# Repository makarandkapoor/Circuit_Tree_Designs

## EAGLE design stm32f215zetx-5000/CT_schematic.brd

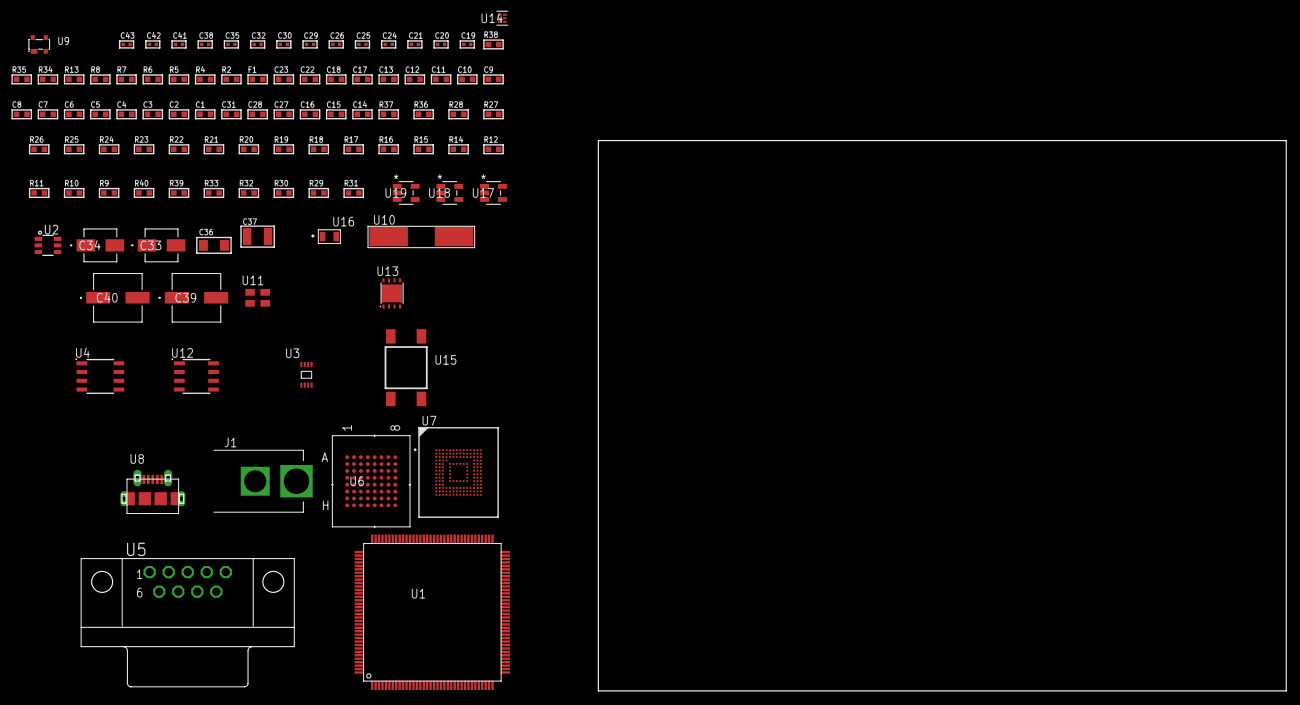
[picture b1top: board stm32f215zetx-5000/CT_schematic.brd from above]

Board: 2 copper layers, 102 parts (0 on the bottom side), 98 nets, no tracks yet.

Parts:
C1, C18, C22, C23: 1e-06; C0603
C2, C3, C4, C5, C6, C7, C8, C9, C10, C11, C12, C13: 1e-07; C0603
C14: 4.7e-06; C0603
C15, C16, C27, C28, C31: 2.2e-06; C0603
C17: 1e-08; C0603
C19, C20: 1e-11; C0402
C21, C24, C25, C32, C35, C41, C42, C43: 1e-08; C0402
C26, C29, C30, C38: 1e-07; C0402
C33: 1e-06; EXV-9B
C34: 2.2e-06; EXV-9B
C36: 1e-05; C1206
C37: 1e-05; C1210
C39, C40: 0.0001; EXV-9H
F1: 240.0; L0603
J1: PJ-037B; PJ-037B_PACKAGE
R2, R35: 1000.0; R0603
R4, R5, R6: 4700.0; R0603
R7, R8: 2200.0; R0603
R9: 47000.0; R0603
R10, R11, R12, R14, R15, R16, R17, R18, R36, R37: 10000.0; R0603
R13: 120.0; R0603
R19, R20, R21, R22, R23, R24, R25, R26, R27, R28: 34000.0; R0603
R29, R30, R32, R33: 100000.0; R0603
R31: 164658.62; R0603
R34: 3900.0; R0603
R38: 9100.0; R0603
R39: 680000.0; R0603
R40: 120000.0; R0603
U1: STM32F215ZET6; LQFP144
U2: MAX4995AAUT+T; SOT-23-6
U3: 24AA01T-I/MNY; TDFN-8/6MM
U4: MCP2562-E/SN; SOIC-8
U5: 182-009-113R531; 182-009-MALE
U6: mt28ew512aba1HPC-0AAT; LBGA-64
U7: mtfc4gmcdm; TFBGA-153
U8: 47590-0001; MICRO_USB_AB
U9: prtr5v0u2ax; SOT143B
U10: ABLS-25.000MHZ-B2F-T
U11: ASEK-32.768KHz-ECST; ASEK
U12: LP2954AIMX/NOPB; LP2954
U13: LP3878SDX-ADJ/NOPB; WSON-8
U14: TPS3895ADRYR; SON-6
U15: 4-1437565-2; SW_4-1437565-2
U16: Q65110A2395; LGM67K-G1J2-24-Z
U17, U18, U19: nc7sz125m5x; NC7SZ125M5X

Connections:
CLK_CRYSTAL_U1_23: C19.1, U1.23, U10.1
CLK_CRYSTAL_U1_24: C20.1, U1.24, U10.2
CLK_U1_8: U1.8, U11.3
GND: C1.2, C2.2, C3.2, C4.2, C5.2, C6.2, C7.2, C8.2, C9.2, C10.2, C11.2, C12.2, C13.2, C14.2, C15.2, C16.2, C17.2, C18.2, C19.2, C20.2, C21.2, C22.2, C23.2, C24.2, C25.2, C26.2, C27.2, C28.2, C29.2, C30.2, C31.2, C32.2, C33.2, C34.2, C35.2, C36.2, C37.2, C38.2, C39.2, C40.2, C41.2, C42.2, C43.2, J1.2, R2.2, R9.2, R10.2, R12.2, R32.2, R35.2, R38.2, R40.2, U1.16, U1.31, U1.38, U1.51, U1.61, U1.83, U1.94, U1.107, U1.120, U1.130, U2.2, U3.4, U4.2, U4.8, U5.5, U6.E8, U6.H2, U6.H7, U7.C4, U7.E7, U7.G5, U7.H10, U7.K8, U7.N2, U7.N5, U7.P4, U7.P6, U8.5, U8.6, U8.7, U8.8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
NET_U1_25: R6.1, U1.25, U19.4
NET_U1_33: C17.1, C18.1, F1.1, U1.32, U1.33
NET_U1_71: C15.1, U1.71
NET_U1_106: C16.1, U1.106
NET_U1_136: R7.1, U1.136, U3.6
NET_U1_137: R8.1, U1.137, U3.5
NET_U1_138: R10.1, U1.138
NET_U1_142: U15.3, U15.4
NET_U2_1: U1.101, U2.1
NET_U2_3: R9.1, U2.3
NET_U4_6: R13.2, U4.6
NET_U5_2: R13.2, U4.6, U5.2
NET_U5_3: R13.1, U4.7, U5.3
NET_U6_B4: R17.1, U6.B4
NET_U6_B5: R4.1, U6.B5, U17.4
NET_U6_F7: R18.1, U6.F7
NET_U7_C2: C28.1, C29.1, U7.C2
NET_U7_K5: R5.1, U7.K5, U18.4
NET_U12_3: R30.1, U12.3
NET_U12_5: R29.1, U12.5
NET_U12_7: R31.2, R32.1, U12.7
NET_U13_1: C35.1, U13.1
NET_U13_6: R34.2, R35.1, U13.6
NET_U13_8: R33.1, U13.8
NET_U14_1: R37.1, R38.1, U14.1
NET_U14_3: R39.2, R40.1, U14.3
NET_U14_4: R36.1, U14.4, U17.2, U18.2, U19.2
NET_U15_1: R2.1, U15.1, U15.2
PROC_CAN1_RX: U1.103, U4.4
PROC_CAN1_TX: U1.104, U4.1
PROC_FSMC_A0: U1.10, U6.E2
PROC_FSMC_A1: U1.11, U6.D2
PROC_FSMC_A2: U1.12, U6.C2
PROC_FSMC_A3: U1.13, U6.A2
PROC_FSMC_A4: U1.14, U6.B2
PROC_FSMC_A5: U1.15, U6.D3
PROC_FSMC_A6: U1.50, U6.C3
PROC_FSMC_A7: U1.53, U6.A3
PROC_FSMC_A8: U1.54, U6.B6
PROC_FSMC_A9: U1.55, U6.A6
PROC_FSMC_A10: U1.56, U6.C6
PROC_FSMC_A11: U1.57, U6.D6
PROC_FSMC_A12: U1.87, U6.B7
PROC_FSMC_A13: U1.88, U6.A7
PROC_FSMC_A14: U1.89, U6.C7
PROC_FSMC_A15: U1.90, U6.D7
PROC_FSMC_A16: U1.80, U6.E7
PROC_FSMC_A17: U1.81, U6.B3
PROC_FSMC_A18: U1.82, U6.C4
PROC_FSMC_A19: U1.2, U6.D5
PROC_FSMC_A20: U1.3, U6.D4
PROC_FSMC_A21: U1.4, U6.C5
PROC_FSMC_A22: U1.5, U6.B8
PROC_FSMC_A23: U1.1, U6.C8
PROC_FSMC_A24: U1.128, U6.F8
PROC_FSMC_D0: U1.85, U6.E3
PROC_FSMC_D1: U1.86, U6.H3
PROC_FSMC_D2: U1.114, U6.E4
PROC_FSMC_D3: U1.115, U6.H4
PROC_FSMC_D4: U1.58, U6.H5
PROC_FSMC_D5: U1.59, U6.E5
PROC_FSMC_D6: U1.60, U6.H6
PROC_FSMC_D7: U1.63, U6.E6
PROC_FSMC_D8: U1.64, U6.F3
PROC_FSMC_D9: U1.65, U6.G3
PROC_FSMC_D10: U1.66, U6.F4
PROC_FSMC_D11: U1.67, U6.G4
PROC_FSMC_D12: U1.68, U6.F5
PROC_FSMC_D13: U1.77, U6.G6
PROC_FSMC_D14: U1.78, U6.F6
PROC_FSMC_D15: U1.79, U6.G7
PROC_FSMC_NE4: R14.1, U1.127, U6.F2
PROC_FSMC_NOE: R15.1, U1.118, U6.G2
PROC_FSMC_NWAIT: U1.122, U6.A4
PROC_FSMC_NWE: R16.1, U1.119, U6.A5
PROC_GPIO_TO_U1_USB_FAULT: R11.1, U1.9, U2.6
PROC_GPIO_TO_U1_VBUS_EN: R12.1, U1.7, U2.4
PROC_SDIO_CK: R28.1, U1.113, U7.M6
PROC_SDIO_CMD: R27.1, U1.116, U7.M5
PROC_SDIO_D0: R19.1, U1.98, U7.A3
PROC_SDIO_D1: R20.1, U1.99, U7.A4
PROC_SDIO_D2: R21.1, U1.111, U7.A5
PROC_SDIO_D3: R22.1, U1.112, U7.B2
PROC_SDIO_D4: R23.1, U1.139, U7.B3
PROC_SDIO_D5: R24.1, U1.140, U7.B4
PROC_SDIO_D6: R25.1, U1.96, U7.B5
PROC_SDIO_D7: R26.1, U1.97, U7.B6
PROC_USB_OTG_HS_DM: U1.75, U8.2, U9.3
PROC_USB_OTG_HS_DP: U1.76, U8.3, U9.2
PROC_USB_OTG_HS_ID: U1.73, U8.4
PROC_USB_OTG_HS_VBUS: U1.74, U8.1, U9.4
VCC_S1_10V6: C33.1, C36.1, C39.1, C40.1, J1.1, R30.2, R33.2, U12.8, U13.4
VCC_TIER1_3V3: C1.1, C2.1, C3.1, C4.1, C5.1, C6.1, C7.1, C8.1, C9.1, C10.1, C11.1, C12.1, C13.1, C14.1, C21.1, C23.1, C24.1, C25.1, C26.1, C27.1, C30.1, C31.1, C32.1, C34.1, C38.1, C41.1, C42.1, C43.1, F1.2, R4.2, R5.2, R6.2, R7.2, R8.2, R11.2, R14.2, R15.2, R16.2, R17.2, R18.2, R19.2, R20.2, R21.2, R22.2, R23.2, R24.2, R25.2, R26.2, R27.2, R28.2, R29.2, R31.1, R36.2, R37.2, R39.1, U1.6, U1.17, U1.30, U1.39, U1.52, U1.62, U1.72, U1.84, U1.95, U1.108, U1.121, U1.131, U1.144, U3.7, U3.8, U4.5, U6.D8, U6.F1, U6.G5, U7.C6, U7.E6, U7.F5, U7.J10, U7.K9, U7.M4, U7.N4, U7.P3, U7.P5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
VCC_TIER1_5V0: C22.1, C37.1, R34.1, U2.5, U4.3, U13.5

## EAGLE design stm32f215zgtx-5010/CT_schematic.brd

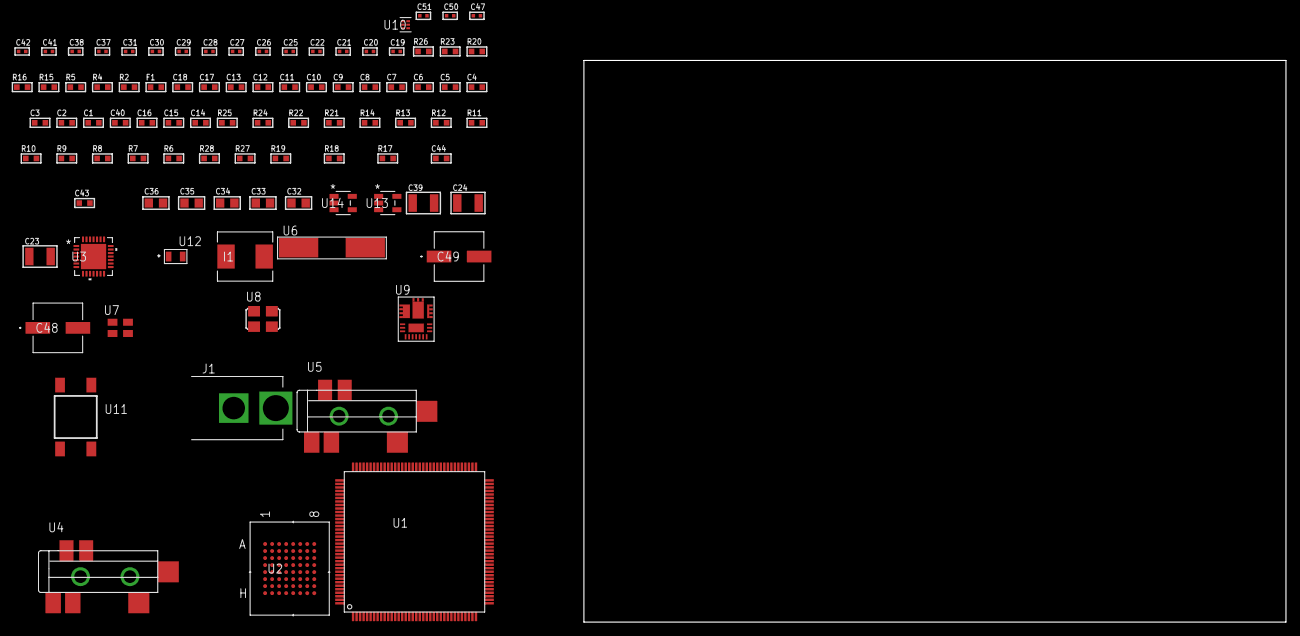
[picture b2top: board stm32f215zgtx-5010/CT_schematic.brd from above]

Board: 2 copper layers, 100.0 x 80.0 mm, 92 parts (0 on the bottom side), 82 nets, no tracks yet.

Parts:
C1, C18: 1e-06; C0603
C2, C3, C4, C5, C6, C7, C8, C9, C10, C11, C12, C13: 1e-07; C0603
C14: 4.7e-06; C0603
C15, C16, C40: 2.2e-06; C0603
C17: 1e-08; C0603
C19, C20: 1e-11; C0402
C21, C22, C37, C38, C50, C51: 1e-08; C0402
C23, C24: 2.2e-05; C1210
C25, C26: 1e-09; C0402
C27, C28, C29, C30, C31, C41, C42, C47: 1e-07; C0402
C32, C33, C34, C35, C36: 1e-05; C0805
C39: 0.0001; C1210
C43: 8.8006443804346e-09; R0603
C44: 3.0002196751482e-07; R0603
C48, C49: 0.0001; EXV-9H
F1: 240.0; L0603
I1: 6.8e-07; IND25X25CZ
J1: PJ-037B; PJ-037B_PACKAGE
R2: 1000.0; R0603
R4, R5: 4700.0; R0603
R6, R7, R8, R9, R10, R11, R24, R25: 10000.0; R0603
R12, R13, R14: 47000.0; R0603
R15: 680.0; R0603
R16: 0.1; R0603
R17: 4030.2416170974; R0603
R18: 719.68600305311; R0603
R19: 57.923764705882; R0603
R20: 130.0; R0603
R21: 39000.0; R0603
R22: 49900.0; R0603
R23: 5100.0; R0603
R26: 9100.0; R0603
R27: 680000.0; R0603
R28: 120000.0; R0603
U1: STM32F215ZGT7; LQFP144
U2: mt28ew512aba1HPC-0AAT; LBGA-64
U3: WM8731CLSEFL; QFN-28
U4, U5: SJ-43515TS-SMT-TR
U6: ABLS-25.000MHZ-B2F-T
U7: ASEK-32.768KHz-ECST; ASEK
U8: ASFL1-12.288MHZ-EC-T; ASFL1
U9: IR3899MTR1PBF
U10: TPS3895ADRYR; SON-6
U11: 4-1437565-2; SW_4-1437565-2
U12: Q65110A2395; LGM67K-G1J2-24-Z
U13, U14: nc7sz125m5x; NC7SZ125M5X

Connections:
CLK_CRYSTAL_U1_23: C19.1, U1.23, U6.1
CLK_CRYSTAL_U1_24: C20.1, U1.24, U6.2
CLK_U1_8: U1.8, U7.3
CLK_U3_1: U3.1, U8.3
GND: C1.2, C2.2, C3.2, C4.2, C5.2, C6.2, C7.2, C8.2, C9.2, C10.2, C11.2, C12.2, C13.2, C14.2, C15.2, C16.2, C17.2, C18.2, C19.2, C20.2, C21.2, C22.2, C26.2, C27.2, C28.2, C29.2, C30.2, C31.2, C32.2, C33.2, C34.2, C35.2, C36.2, C37.2, C38.2, C40.2, C41.2, C42.2, C47.2, C48.2, C49.2, C50.2, C51.2, J1.2, R2.2, R6.2, R12.2, R13.2, R14.2, R16.1, R16.2, R18.2, R21.2, R23.2, R26.2, R28.2, U1.16, U1.31, U1.38, U1.51, U1.61, U1.83, U1.94, U1.107, U1.120, U1.130, U2.E8, U2.H2, U2.H7, U3.4, U3.15, U3.19, U3.25, U3.26, U3.29, U4.1, U5.1, U7.2, U8.2, U9.4, U9.11, U9.17, U10.2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
NET_U1_25: R5.1, U1.25, U14.4
NET_U1_33: C17.1, C18.1, F1.1, U1.32, U1.33
NET_U1_71: C15.1, U1.71
NET_U1_106: C16.1, U1.106
NET_U1_138: R6.1, U1.138
NET_U1_142: U11.3, U11.4
NET_U2_B4: R10.1, U2.B4
NET_U2_B5: R4.1, U2.B5, U13.4
NET_U2_F7: R11.1, U2.F7
NET_U3_20: C31.1, C36.1, U3.20
NET_U4_2: C24.1, R13.1, U4.2
NET_U4_5: C23.1, R12.1, U4.5
NET_U5_5: C25.1, C26.1, R14.1, R15.1, U5.5
NET_U9_1: C43.1, R17.1, R18.1, R19.1, R20.1, U9.1, U9.8
NET_U9_2: C42.1, U9.2
NET_U9_3: C43.2, C44.1, C44.2, U9.3
NET_U9_5: R21.1, U9.5
NET_U9_10: C40.1, U9.10
NET_U9_12: C39.1, I1.1, U9.12
NET_U9_14: C39.2, U9.14
NET_U9_15: R22.1, R23.1, U9.15
NET_U9_ATNET_3: I1.2, R17.2
NET_U9_ATNET_4: C44.2, R19.2
NET_U10_1: R25.1, R26.1, U10.1
NET_U10_3: R27.2, R28.1, U10.3
NET_U10_4: R24.1, U10.4, U13.2, U14.2
NET_U11_1: R2.1, U11.1, U11.2
PROC_FSMC_A0: U1.10, U2.E2
PROC_FSMC_A1: U1.11, U2.D2
PROC_FSMC_A2: U1.12, U2.C2
PROC_FSMC_A3: U1.13, U2.A2
PROC_FSMC_A4: U1.14, U2.B2
PROC_FSMC_A5: U1.15, U2.D3
PROC_FSMC_A6: U1.50, U2.C3
PROC_FSMC_A7: U1.53, U2.A3
PROC_FSMC_A8: U1.54, U2.B6
PROC_FSMC_A9: U1.55, U2.A6
PROC_FSMC_A10: U1.56, U2.C6
PROC_FSMC_A11: U1.57, U2.D6
PROC_FSMC_A12: U1.87, U2.B7
PROC_FSMC_A13: U1.88, U2.A7
PROC_FSMC_A14: U1.89, U2.C7
PROC_FSMC_A15: U1.90, U2.D7
PROC_FSMC_A16: U1.80, U2.E7
PROC_FSMC_A17: U1.81, U2.B3
PROC_FSMC_A18: U1.82, U2.C4
PROC_FSMC_A19: U1.2, U2.D5
PROC_FSMC_A20: U1.3, U2.D4
PROC_FSMC_A21: U1.4, U2.C5
PROC_FSMC_A22: U1.5, U2.B8
PROC_FSMC_A23: U1.1, U2.C8
PROC_FSMC_A24: U1.128, U2.F8
PROC_FSMC_D0: U1.85, U2.E3
PROC_FSMC_D1: U1.86, U2.H3
PROC_FSMC_D2: U1.114, U2.E4
PROC_FSMC_D3: U1.115, U2.H4
PROC_FSMC_D4: U1.58, U2.H5
PROC_FSMC_D5: U1.59, U2.E5
PROC_FSMC_D6: U1.60, U2.H6
PROC_FSMC_D7: U1.63, U2.E6
PROC_FSMC_D8: U1.64, U2.F3
PROC_FSMC_D9: U1.65, U2.G3
PROC_FSMC_D10: U1.66, U2.F4
PROC_FSMC_D11: U1.67, U2.G4
PROC_FSMC_D12: U1.68, U2.F5
PROC_FSMC_D13: U1.77, U2.G6
PROC_FSMC_D14: U1.78, U2.F6
PROC_FSMC_D15: U1.79, U2.G7
PROC_FSMC_NE4: R7.1, U1.127, U2.F2
PROC_FSMC_NOE: R8.1, U1.118, U2.G2
PROC_FSMC_NWAIT: U1.122, U2.A4
PROC_FSMC_NWE: R9.1, U1.119, U2.A5
PROC_I2S2_SCK: U1.69, U3.7
PROC_I2S2_SD: U1.29, U3.8
PROC_I2S2_WS: U1.73, U3.9, U3.11
VCC_S1_17V0: C41.1, C48.1, C49.1, J1.1, R22.2, U9.9
VCC_TIER1_3V3: C1.1, C2.1, C3.1, C4.1, C5.1, C6.1, C7.1, C8.1, C9.1, C10.1, C11.1, C12.1, C13.1, C14.1, C21.1, C22.1, C27.1, C28.1, C29.1, C30.1, C32.1, C33.1, C34.1, C35.1, C37.1, C38.1, C47.1, C50.1, C51.1, F1.2, I1.2, R4.2, R5.2, R7.2, R8.2, R9.2, R10.2, R11.2, R17.2, R24.2, R25.2, R27.1, U1.6, U1.17, U1.30, U1.39, U1.52, U1.62, U1.72, U1.84, U1.95, U1.108, U1.121, U1.131, U1.144, U2.D8, U2.F1, U2.G5, U3.3, U3.5, U3.12, U3.18, U7.4, U8.4, U10.6, U13.5, U14.5

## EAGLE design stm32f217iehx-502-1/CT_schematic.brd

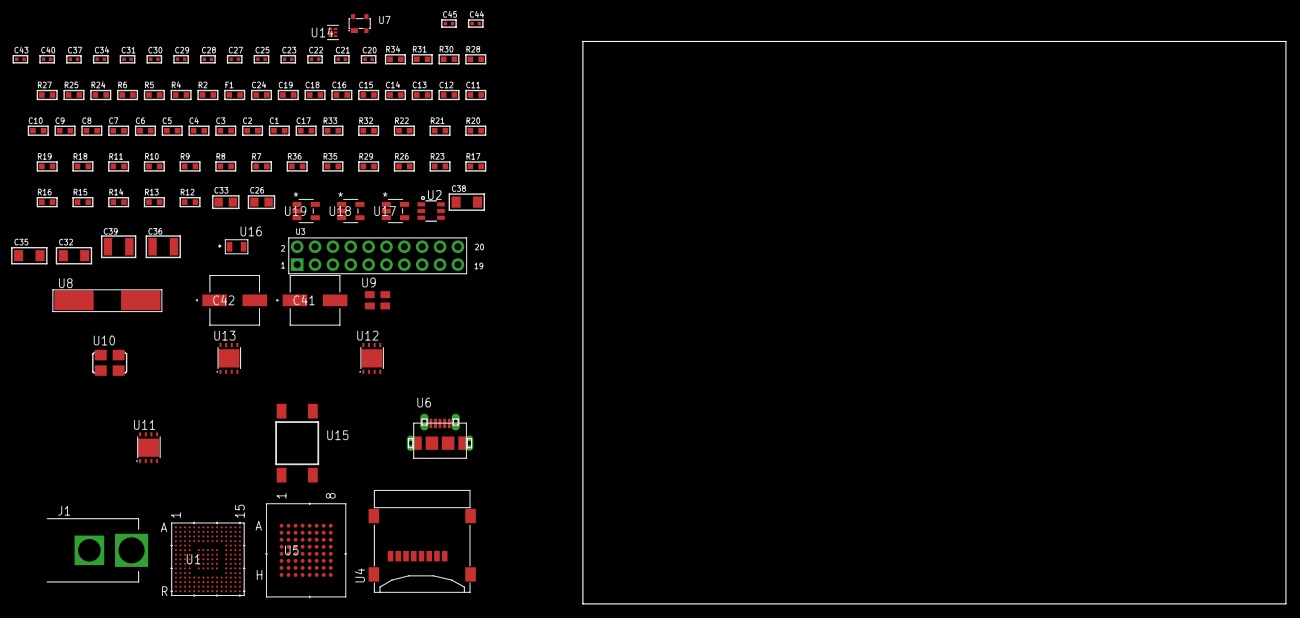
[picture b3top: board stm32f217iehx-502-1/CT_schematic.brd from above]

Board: 2 copper layers, 124.8 x 80.0 mm, 100 parts (0 on the bottom side), 100 nets, no tracks yet.

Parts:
C1, C19, C24: 1e-06; C0603
C2, C3, C4, C5, C6, C7, C8, C9, C10, C11, C12, C13, C14, C15, C16: 1e-07; C0603
C17: 4.7e-06; C0603
C18: 1e-08; C0603
C20, C21, C25, C40: 1e-07; C0402
C22, C23: 1e-11; C0402
C26, C33: 1e-05; C0805
C27, C28, C29, C30, C31, C34, C37, C43, C44, C45: 1e-08; C0402
C32, C35, C38: 1e-05; C1206
C36, C39: 1e-05; C1210
C41, C42: 0.0001; EXV-9H
F1: 240.0; L0603
J1: PJ-037B; PJ-037B_PACKAGE
R2, R25, R28, R31: 1000.0; R0603
R4, R5, R6: 4700.0; R0603
R7: 47000.0; R0603
R8, R9, R10, R11, R18, R19, R20, R21, R22, R32, R33: 10000.0; R0603
R12, R13, R14, R15, R16, R17, R23, R26, R29: 100000.0; R0603
R24: 200.0; R0603
R27: 2231.0; R0603
R30: 3900.0; R0603
R34: 9100.0; R0603
R35: 680000.0; R0603
R36: 120000.0; R0603
U1: STM32F217IEH6; UFBGA176_25
U2: MAX4995AAUT+T; SOT-23-6
U3: arducam_ov2640; ARDUCAM
U4: 0472192001; MOLEX_47219-2001
U5: MT28EW128ABA1HPC-0SIT; LBGA-64
U6: 47590-0001; MICRO_USB_AB
U7: prtr5v0u2ax; SOT143B
U8: ABLS-25.000MHZ-B2F-T
U9: ASEK-32.768KHz-ECST; ASEK
U10: ASFL1-25MHZ-NCS; ASFL1
U11, U12, U13: LP3878SDX-ADJ/NOPB; WSON-8
U14: TPS3895ADRYR; SON-6
U15: 4-1437565-2; SW_4-1437565-2
U16: Q65110A2395; LGM67K-G1J2-24-Z
U17, U18, U19: nc7sz125m5x; NC7SZ125M5X

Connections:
CLK_CRYSTAL_U1_G1: C22.1, U1.G1, U8.1
CLK_CRYSTAL_U1_H1: C23.1, U1.H1, U8.2
CLK_U1_E1: U1.E1, U9.3
CLK_U3_8: U3.8, U10.3
GND: C1.2, C2.2, C3.2, C4.2, C5.2, C6.2, C7.2, C8.2, C9.2, C10.2, C11.2, C12.2, C13.2, C14.2, C15.2, C16.2, C17.2, C18.2, C19.2, C20.2, C21.2, C22.2, C23.2, C24.2, C25.2, C26.2, C27.2, C28.2, C29.2, C30.2, C31.2, C32.2, C33.2, C34.2, C35.2, C36.2, C37.2, C38.2, C39.2, C40.2, C41.2, C42.2, C43.2, C44.2, C45.2, J1.2, R2.2, R7.2, R8.2, R11.2, R25.2, R28.2, R31.2, R34.2, R36.2, U1.D5, U1.D7, U1.D8, U1.D9, U1.F2, U1.F6, U1.F7, U1.F8, U1.F9, U1.F10, U1.F12, U1.G2, U1.G6, U1.G7, U1.G8, U1.G9, U1.G10, U1.G12, U1.H6, U1.H7, U1.H8, U1.H9, U1.H10, U1.H12, U1.J6, U1.J7, U1.J8, U1.J9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
NET_U1_D6: R8.1, U1.D6
NET_U1_F13: C21.1, U1.F13
NET_U1_J1: R5.1, U1.J1, U18.4
NET_U1_L4: R9.1, U1.L4
NET_U1_R1: C18.1, C19.1, F1.1, U1.P1, U1.R1
NET_U1_R15: U15.3, U15.4
NET_U2_3: R7.1, U2.3
NET_U3_19: R6.1, U3.19, U19.4
NET_U5_B4: R21.1, U5.B4
NET_U5_B5: R4.1, U5.B5, U17.4
NET_U11_1: C31.1, U11.1
NET_U11_6: R24.2, R25.1, U11.6
NET_U11_8: R23.1, U11.8
NET_U12_1: C34.1, U12.1
NET_U12_6: R27.2, R28.1, U12.6
NET_U12_8: R26.1, U12.8
NET_U13_1: C37.1, U13.1
NET_U13_6: R30.2, R31.1, U13.6
NET_U13_8: R29.1, U13.8
NET_U14_1: R33.1, R34.1, U14.1
NET_U14_3: R35.2, R36.1, U14.3
NET_U14_4: R32.1, U14.4, U17.2, U18.2, U19.2
NET_U15_1: R2.1, U15.1, U15.2
PROC_DCMI_D0: U1.H15, U3.18
PROC_DCMI_D1: U1.G15, U3.17
PROC_DCMI_D2: U1.L12, U3.16
PROC_DCMI_D3: U1.A3, U3.15
PROC_DCMI_D4: U1.E13, U3.14
PROC_DCMI_D5: U1.B6, U3.13
PROC_DCMI_D6: U1.A5, U3.12
PROC_DCMI_D7: U1.B4, U3.11
PROC_DCMI_D8: U1.D14, U3.10
PROC_DCMI_D9: U1.C14, U3.9
PROC_DCMI_HSYNC: U1.M12, U3.6
PROC_DCMI_PIXCK: U1.P3, U3.7
PROC_DCMI_VSYNC: U1.B5, U3.5
PROC_FSMC_A0: U1.E2, U5.E2
PROC_FSMC_A1: U1.H3, U5.D2
PROC_FSMC_A2: U1.H2, U5.C2
PROC_FSMC_A3: U1.J2, U5.A2
PROC_FSMC_A4: U1.J3, U5.B2
PROC_FSMC_A5: U1.K3, U5.D3
PROC_FSMC_A6: U1.P6, U5.C3
PROC_FSMC_A7: U1.N6, U5.A3
PROC_FSMC_A8: U1.R7, U5.B6
PROC_FSMC_A9: U1.P7, U5.A6
PROC_FSMC_A10: U1.N7, U5.C6
PROC_FSMC_A11: U1.M7, U5.D6
PROC_FSMC_A12: U1.L15, U5.B7
PROC_FSMC_A13: U1.K15, U5.A7
PROC_FSMC_A14: U1.K14, U5.C7
PROC_FSMC_A15: U1.K13, U5.D7
PROC_FSMC_A16: U1.N14, U5.E7
PROC_FSMC_A17: U1.N13, U5.B3
PROC_FSMC_A18: U1.M15, U5.C4
PROC_FSMC_A19: U1.A1, U5.D5
PROC_FSMC_A20: U1.B1, U5.D4
PROC_FSMC_A21: U1.B2, U5.C5
PROC_FSMC_A22: U1.B3, U5.B8
PROC_FSMC_D0: U1.M14, U5.E3
PROC_FSMC_D1: U1.L14, U5.H3
PROC_FSMC_D2: U1.B12, U5.E4
PROC_FSMC_D3: U1.C12, U5.H4
PROC_FSMC_D4: U1.R8, U5.H5
PROC_FSMC_D5: U1.P8, U5.E5
PROC_FSMC_D6: U1.P9, U5.H6
PROC_FSMC_D7: U1.R9, U5.E6
PROC_FSMC_D8: U1.P10, U5.F3
PROC_FSMC_D9: U1.R10, U5.G3
PROC_FSMC_D10: U1.N11, U5.F4
PROC_FSMC_D11: U1.P11, U5.G4
PROC_FSMC_D12: U1.R11, U5.F5
PROC_FSMC_D13: U1.P15, U5.G6
PROC_FSMC_D14: U1.P14, U5.F6
PROC_FSMC_D15: U1.N15, U5.G7
PROC_FSMC_NBL0: R22.1, U1.A4, U5.F7
PROC_FSMC_NE4: R18.1, U1.B8, U5.F2
PROC_FSMC_NOE: R19.1, U1.D10, U5.G2
PROC_FSMC_NWAIT: U1.B11, U5.A4
PROC_FSMC_NWE: R20.1, U1.C11, U5.A5
PROC_GPIO_TO_U1_USB_FAULT: R10.1, U1.A6, U2.6
PROC_GPIO_TO_U1_VBUS_EN: R11.1, U1.A2, U2.4
PROC_SDIO_CK: R13.1, U1.A12, U4.5
PROC_SDIO_CMD: R12.1, U1.D12, U4.3
PROC_SDIO_D0: R14.1, U1.G14, U4.7
PROC_SDIO_D1: R15.1, U1.F14, U4.8
PROC_SDIO_D2: R16.1, U1.B14, U4.1
PROC_SDIO_D3: R17.1, U1.B13, U4.2
PROC_USB_OTG_FS_DM: U6.2, U7.3
PROC_USB_OTG_FS_DP: U6.3, U7.2
PROC_USB_OTG_FS_VBUS: U2.1, U6.1, U7.4
VCC_S1_9V5: C32.1, C35.1, C38.1, C41.1, C42.1, J1.1, R23.2, R26.2, R29.2, U11.4, U12.4, U13.4
VCC_TIER1_1V2: C20.1, C33.1, R24.1, U1.M10, U11.5
VCC_TIER1_3V3: C1.1, C2.1, C3.1, C4.1, C5.1, C6.1, C7.1, C8.1, C9.1, C10.1, C11.1, C12.1, C13.1, C14.1, C15.1, C16.1, C17.1, C24.1, C25.1, C26.1, C27.1, C28.1, C29.1, C30.1, C36.1, C40.1, C43.1, C44.1, C45.1, F1.2, R4.2, R5.2, R6.2, R9.2, R10.2, R12.2, R13.2, R14.2, R15.2, R16.2, R17.2, R18.2, R19.2, R20.2, R21.2, R22.2, R27.1, R32.2, R33.2, R35.1, U1.C1, U1.C5, U1.C7, U1.C8, U1.C9, U1.F3, U1.G3, U1.G13, U1.H13, U1.J12, U1.J13, U1.K4, U1.N8, U1.N9, U1.N10, U3.1, U4.4, U5.D8, U5.F1, U5.G5, U9.4, U10.4, U12.5, U14.6, U17.5, U18.5, U19.5
VCC_TIER1_5V0: C39.1, R30.1, U2.5, U13.5

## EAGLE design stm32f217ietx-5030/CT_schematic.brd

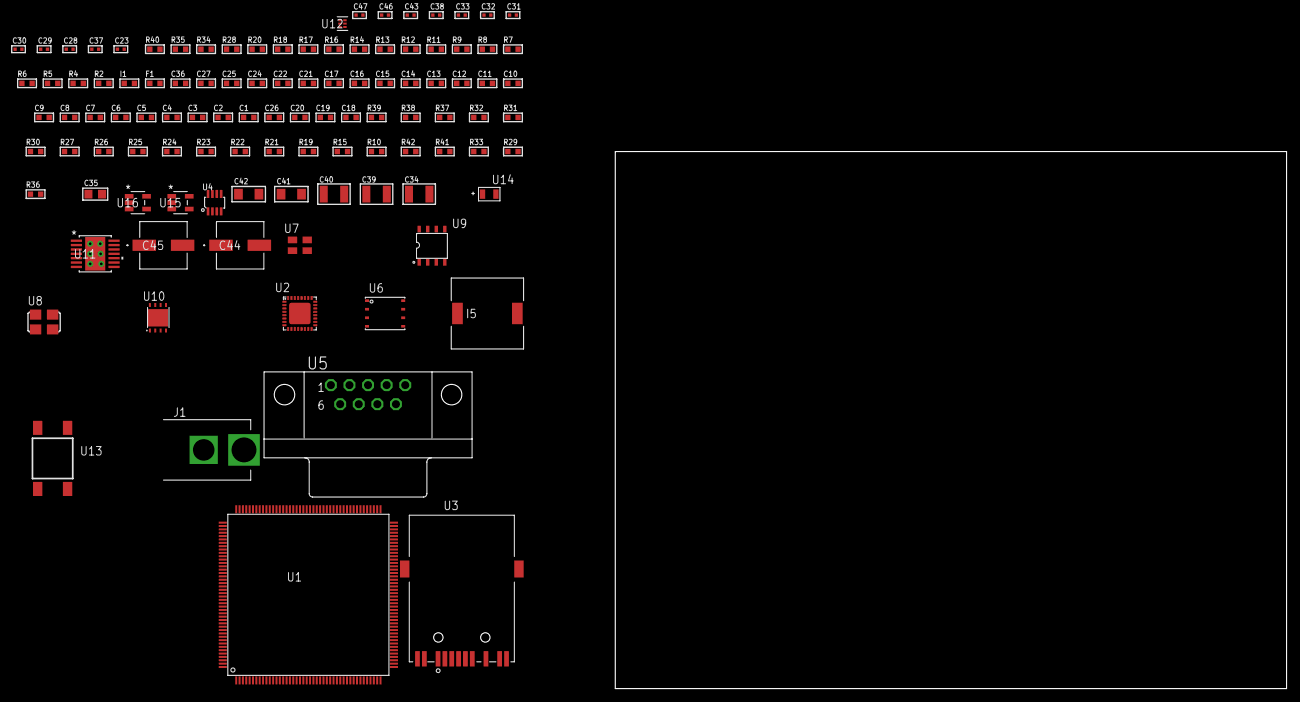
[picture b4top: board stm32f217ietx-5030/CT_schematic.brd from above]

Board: 2 copper layers, 100.0 x 80.0 mm, 107 parts (0 on the bottom side), 69 nets, no tracks yet.

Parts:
C1, C22, C24, C25, C27, C36: 1e-06; C0603
C2, C3, C4, C5, C6, C7, C8, C9, C10, C11, C12, C13, C14, C15, C16, C17: 1e-07; C0603
C18: 4.7e-06; C0603
C19, C20: 2.2e-06; C0603
C21: 1e-08; C0603
C23: 2.2e-08; C0402
C26: 4.7e-10; C0603
C28, C38, C43: 1e-07; C0402
C29, C30, C31, C32, C33, C46, C47: 1e-08; C0402
C34: 1e-05; C1210
C35: 1e-05; C0805
C37: 3.3e-09; C0402
C39, C40: 2.2e-05; C1210
C41, C42: 1e-05; C1206
C44, C45: 0.0001; EXV-9H
F1: 240.0; L0603
I1: 97.0; R0603
I5: 5.2e-06; DR1040
J1: PJ-037B; PJ-037B_PACKAGE
R2, R35: 1000.0; R0603
R4, R5: 4700.0; R0603
R6, R7, R8, R9: 2200.0; R0603
R10, R19, R21, R22, R23, R24, R25, R26, R27, R30, R31, R32, R38, R39: 10000.0; R0603
R11, R12: 0.1; R0603
R13, R14, R34: 200.0; R0603
R15: 12100.0; R0603
R16, R17, R18, R20: 49.9; R0603
R28: 120.0; R0603
R29, R33: 100000.0; R0603
R36: 71007.101651032; R0603
R37: 22000.0; R0603
R40: 9100.0; R0603
R41: 680000.0; R0603
R42: 120000.0; R0603
U1: STM32F217IET6; LQFP176
U2: LAN8710AI-EZK; QFN-32
U3: 7498011122R
U4: MAX3051EKA+T; SOT-23-8
U5: 182-009-113R531; 182-009-MALE
U6: 24AA512-I/MF; DFN8-S
U7: ASEK-32.768KHz-ECST; ASEK
U8: ASFL1-25MHZ-NCS; ASFL1
U9: idt74fct38072; IDT74FCT38072
U10: LP3878SDX-ADJ/NOPB; WSON-8
U11: tps54325PWP; HTSSOP14
U12: TPS3895ADRYR; SON-6
U13: 4-1437565-2; SW_4-1437565-2
U14: Q65110A2395; LGM67K-G1J2-24-Z
U15, U16: nc7sz125m5x; NC7SZ125M5X

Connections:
CLK_U1_9: U1.9, U7.3
CLK_U1_29: U1.29, U9.7
CLK_U2_5: U2.5, U9.6
CLK_U9_3: U8.3, U9.3
GND: C1.2, C2.2, C3.2, C4.2, C5.2, C6.2, C7.2, C8.2, C9.2, C10.2, C11.2, C12.2, C13.2, C14.2, C15.2, C16.2, C17.2, C18.2, C19.2, C20.2, C21.2, C22.2, C23.2, C24.2, C25.2, C26.2, C27.2, C28.2, C29.2, C30.2, C31.2, C32.2, C33.2, C34.2, C35.2, C36.2, C37.2, C39.2, C40.2, C41.2, C42.2, C43.2, C44.2, C45.2, C46.2, C47.2, J1.2, R2.2, R10.2, R11.2, R12.2, R13.2, R15.2, R26.2, R27.2, R29.2, R31.2, R32.2, R35.2, R37.2, R40.2, R42.2, U1.14, U1.22, U1.37, U1.48, U1.61, U1.71, U1.90, U1.102, U1.113, U1.126, U1.135, U1.148, U1.158, U2.EXP, U4.2, U5.5, U6.4, U6.7, U7.2, U8.2, U9.4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
NET_U1_31: R5.1, U1.31, U16.4
NET_U1_33: R8.1, U1.33, U2.17
NET_U1_39: C21.1, C22.1, F1.1, U1.38, U1.39
NET_U1_42: R9.1, U1.42, U2.16
NET_U1_81: C19.1, U1.81
NET_U1_125: C20.1, U1.125
NET_U1_164: R6.1, U1.164, U6.6
NET_U1_165: R7.1, U1.165, U6.5
NET_U1_166: R10.1, U1.166
NET_U1_176: U13.3, U13.4
NET_U2_1: C24.1, I1.1, R16.2, R17.2, R18.2, R20.2, R21.2, U2.1, U2.27, U3.2, U3.9
NET_U2_3: R21.1, U2.3
NET_U2_18: R19.1, U2.18
NET_U2_19: R4.1, U2.19, U15.4
NET_U2_32: R15.1, U2.32
NET_U3_1: R16.1, U2.29, U3.1
NET_U3_3: R14.2, R17.1, U2.28, U3.3
NET_U3_4: R18.1, U2.31, U3.4
NET_U3_5: C23.1, U3.2, U3.5
NET_U3_6: R20.1, U2.30, U3.6
NET_U3_8: R12.1, U3.8
NET_U3_10: R14.1, U3.10
NET_U3_11: U2.2, U3.11
NET_U3_12: R13.1, U3.12
NET_U3_13: R11.1, U3.13, U3.14
NET_U4_6: R28.2, U4.6
NET_U4_8: R29.1, U4.8
NET_U5_2: R28.2, U4.6, U5.2
NET_U5_3: R28.1, U4.7, U5.3
NET_U6_1: R30.1, U6.1
NET_U6_2: R31.1, U6.2
NET_U6_3: R32.1, U6.3
NET_U10_1: C33.1, U10.1
NET_U10_6: R34.2, R35.1, U10.6
NET_U10_8: R33.1, U10.8
NET_U11_2: R36.2, R37.1, U11.2
NET_U11_3: C36.1, U11.3
NET_U11_4: C37.1, U11.4
NET_U11_10: C38.1, I5.1, U11.10, U11.11
NET_U11_12: C38.2, U11.12
NET_U12_1: R39.1, R40.1, U12.1
NET_U12_3: R41.2, R42.1, U12.3
NET_U12_4: R38.1, U12.4, U15.2, U16.2
NET_U13_1: R2.1, U13.1, U13.2
PROC_CAN1_RX: U1.11, U4.4
PROC_CAN1_TX: U1.123, U4.1
PROC_ETH_COL: R24.1, U1.44, U2.15
PROC_ETH_CRS: U1.40, U2.14
PROC_ETH_RXD0: R22.1, U1.54, U2.11
PROC_ETH_RXD1: R23.1, U1.55, U2.10
PROC_ETH_RXD2: U1.56, U2.9
PROC_ETH_RXD3: R27.1, U1.57, U2.8
PROC_ETH_RX_CLK: R26.1, U1.41, U2.7
PROC_ETH_RX_DV: U1.53, U2.26
PROC_ETH_RX_ER: R25.1, U1.12, U2.13
PROC_ETH_TXD0: U1.92, U2.22
PROC_ETH_TXD1: U1.93, U2.23
PROC_ETH_TXD2: U1.34, U2.24
PROC_ETH_TXD3: U1.1, U2.25
PROC_ETH_TX_CLK: U1.35, U2.20
PROC_ETH_TX_EN: U1.80, U2.21
VCC_S1_11V4: C34.1, C41.1, C42.1, C44.1, C45.1, J1.1, R33.2, U10.4, U11.7, U11.13, U11.14
VCC_TIER1_1V2: C25.1, C26.1, C35.1, R34.1, U2.6, U10.5
VCC_TIER1_3V3: C1.1, C2.1, C3.1, C4.1, C5.1, C6.1, C7.1, C8.1, C9.1, C10.1, C11.1, C12.1, C13.1, C14.1, C15.1, C16.1, C17.1, C18.1, C27.1, C28.1, C29.1, C30.1, C31.1, C32.1, C39.1, C40.1, C43.1, C46.1, C47.1, F1.2, I1.2, I5.2, R4.2, R5.2, R6.2, R7.2, R8.2, R9.2, R19.2, R22.2, R23.2, R24.2, R25.2, R30.2, R36.1, R38.2, R39.2, R41.1, U1.6, U1.15, U1.23, U1.36, U1.49, U1.62, U1.72, U1.82, U1.91, U1.103, U1.114, U1.127, U1.136, U1.149, U1.159, U1.172, U2.12, U4.3, U6.8, U7.4, U8.4, U9.1, U9.2, U11.1, U12.6, U15.5, U16.5

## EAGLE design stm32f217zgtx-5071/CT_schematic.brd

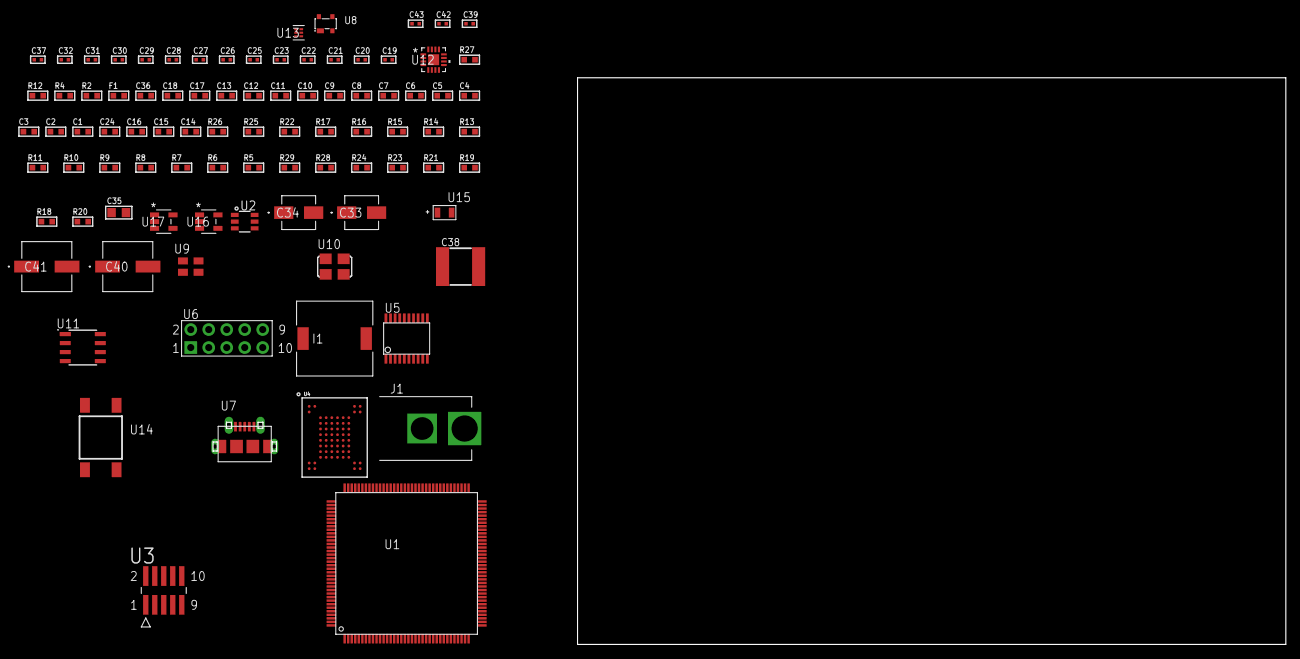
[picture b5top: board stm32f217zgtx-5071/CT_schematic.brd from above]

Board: 2 copper layers, 90 parts (0 on the bottom side), 64 nets, no tracks yet.

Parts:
C1, C18, C36: 1e-06; C0603
C2, C3, C4, C5, C6, C7, C8, C9, C10, C11, C12, C13: 1e-07; C0603
C14: 4.7e-06; C0603
C15, C16, C24: 2.2e-06; C0603
C17: 1e-08; C0603
C19, C20, C21, C22, C23, C25, C26, C27, C28, C29, C30, C37, C39: 1e-07; C0402
C31, C32, C42, C43: 1e-08; C0402
C33: 1e-06; EXV-9B
C34: 2.2e-06; EXV-9B
C35: 1e-05; C0805
C38: 6.8e-05; 2220
C40, C41: 0.0001; EXV-9H
F1: 240.0; L0603
I1: 3.8e-06; DR1040
J1: PJ-037B; PJ-037B_PACKAGE
R2: 1000.0; R0603
R4: 4700.0; R0603
R5: 47000.0; R0603
R6, R7, R8, R9, R10, R11, R13, R14, R15, R16, R17, R25, R26: 10000.0; R0603
R12: 5.0; R0603
R18, R19, R21: 100000.0; R0603
R20: 164658.62; R0603
R22: 20000.0; R0603
R23: 150000.0; R0603
R24: 300000.0; R0603
R27: 9100.0; R0603
R28: 680000.0; R0603
R29: 120000.0; R0603
U1: STM32F217ZGT6; LQFP144
U2: MAX4995AAUT+T; SOT-23-6
U3: FTSH-105-01-L-DV-K; SAMTEC_FTSH-105-01-L-DV-K
U4: mt29f4g08abadah4; VFBGA-63
U5: SP3203ECY-L/TR; TSSOP20-I
U6: HTSS-105-01-G-D
U7: 47590-0001; MICRO_USB_AB
U8: prtr5v0u2ax; SOT143B
U9: ASEK-32.768KHz-ECST; ASEK
U10: ASFL1-25MHZ-NCS; ASFL1
U11: LP2954AIMX/NOPB; LP2954
U12: LTC3601EUD#PBF; QFN-16_EP
U13: TPS3895ADRYR; SON-6
U14: 4-1437565-2; SW_4-1437565-2
U15: Q65110A2395; LGM67K-G1J2-24-Z
U16, U17: nc7sz125m5x; NC7SZ125M5X

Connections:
CLK_U1_8: U1.8, U9.3
CLK_U1_23: U1.23, U10.3
GND: C1.2, C2.2, C3.2, C4.2, C5.2, C6.2, C7.2, C8.2, C9.2, C10.2, C11.2, C12.2, C13.2, C14.2, C15.2, C16.2, C17.2, C18.2, C19.2, C20.2, C21.2, C22.2, C23.2, C24.2, C25.2, C26.2, C29.2, C30.2, C31.2, C32.2, C33.2, C34.2, C35.2, C36.2, C38.1, C38.2, C39.2, C40.2, C41.2, C42.2, C43.2, J1.2, R2.2, R5.2, R6.2, R8.2, R12.2, R21.2, R22.2, R24.2, R27.2, R29.2, U1.16, U1.31, U1.38, U1.51, U1.61, U1.83, U1.94, U1.107, U1.120, U1.130, U2.2, U3.3, U3.5, U4.C5, U4.F7, U4.K3, U4.K8, U5.18, U6.9, U7.5, U7.6, U7.7, U7.8, U7.9, U8.1, U9.2, U10.2, U11.4, U12.1, U12.9, U12.17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
NET_U1_25: R4.1, U1.25, U17.4
NET_U1_33: C17.1, C18.1, F1.1, U1.32, U1.33
NET_U1_71: C15.1, U1.71
NET_U1_106: C16.1, U1.106
NET_U1_138: R6.1, U1.138
NET_U1_142: U14.3, U14.4
NET_U2_3: R5.1, U2.3
NET_U3_9: R12.1, U3.9
NET_U4_C3: R17.1, U4.C3
NET_U5_1: C27.1, U5.1
NET_U5_2: C29.1, U5.2
NET_U5_3: C27.2, U5.3
NET_U5_4: C28.1, U5.4
NET_U5_5: C28.2, U5.5
NET_U5_6: C30.1, U5.6
NET_U6_3: U5.14, U6.3
NET_U6_4: U5.13, U6.4
NET_U6_5: U5.17, U6.5
NET_U6_6: U5.16, U6.6
NET_U11_3: R19.1, U11.3
NET_U11_5: R18.1, U11.5
NET_U11_7: R20.2, R21.1, U11.7
NET_U12_3: C37.2, I1.1, U12.3, U12.4
NET_U12_6: C37.1, U12.6
NET_U12_7: C36.1, U12.7, U12.12
NET_U12_10: R24.1, U12.10
NET_U12_11: R22.1, R23.1, U12.11
NET_U12_ATNET_3: I1.2, R23.2
NET_U13_1: R26.1, R27.1, U13.1
NET_U13_3: R28.2, R29.1, U13.3
NET_U13_4: R25.1, U13.4, U16.4, U17.2
NET_U14_1: R2.1, U14.1, U14.2
PROC_FSMC_A16: U1.80, U4.D5
PROC_FSMC_A17: U1.81, U4.C4
PROC_FSMC_D0: U1.85, U4.H4
PROC_FSMC_D1: U1.86, U4.J4
PROC_FSMC_D2: U1.114, U4.K4
PROC_FSMC_D3: U1.115, U4.K5
PROC_FSMC_D4: U1.58, U4.K6
PROC_FSMC_D5: U1.59, U4.J7
PROC_FSMC_D6: U1.60, U4.K7
PROC_FSMC_D7: U1.63, U4.J8
PROC_FSMC_INT2: R13.1, U1.91, U4.C8
PROC_FSMC_NCE2: R14.1, U1.123, U4.C6
PROC_FSMC_NOE: R16.1, U1.118, U4.D4
PROC_FSMC_NWE: R15.1, U1.119, U4.C7
PROC_GPIO_TO_U1_USB_FAULT: R7.1, U1.2, U2.6
PROC_GPIO_TO_U1_VBUS_EN: R8.1, U1.1, U2.4
PROC_SYS_JTCK_SWCLK: R10.1, U1.109, U3.4
PROC_SYS_JTDO_SWO: U1.133, U3.6
PROC_SYS_JTMS_SWDIO: R11.1, U1.105, U3.2
PROC_UART4_RX: U1.35, U5.11
PROC_UART4_TX: U1.34, U5.7
PROC_USB_OTG_FS_DM: U1.103, U7.2, U8.3
PROC_USB_OTG_FS_DP: U1.104, U7.3, U8.2
PROC_USB_OTG_FS_ID: U1.102, U7.4
PROC_USB_OTG_FS_VBUS: U1.101, U2.1, U7.1, U8.4
RST_OUT_U3_JTAG_RST_B: R9.1, U3.10, U16.1
VCC_S1_6V2: C33.1, C35.1, C40.1, C41.1, J1.1, R19.2, U11.8, U12.15, U12.16
VCC_TIER1_3V3: C1.1, C2.1, C3.1, C4.1, C5.1, C6.1, C7.1, C8.1, C9.1, C10.1, C11.1, C12.1, C13.1, C14.1, C19.1, C20.1, C21.1, C22.1, C23.1, C24.1, C25.1, C26.1, C31.1, C32.1, C34.1, C39.1, C42.1, C43.1, F1.2, R4.2, R7.2, R9.2, R10.2, R11.2, R13.2, R14.2, R15.2, R16.2, R17.2, R18.2, R20.1, R25.2, R26.2, R28.1, U1.6, U1.17, U1.30, U1.39, U1.52, U1.62, U1.72, U1.84, U1.95, U1.108, U1.121, U1.131, U1.144, U3.1, U4.D3, U4.G4, U4.H8, U4.J6, U5.12, U5.19, U9.4, U10.4, U11.1, U13.6, U16.5, U17.5
VCC_TIER1_5V0: C38.2, I1.2, R23.2, U2.5, U12.8

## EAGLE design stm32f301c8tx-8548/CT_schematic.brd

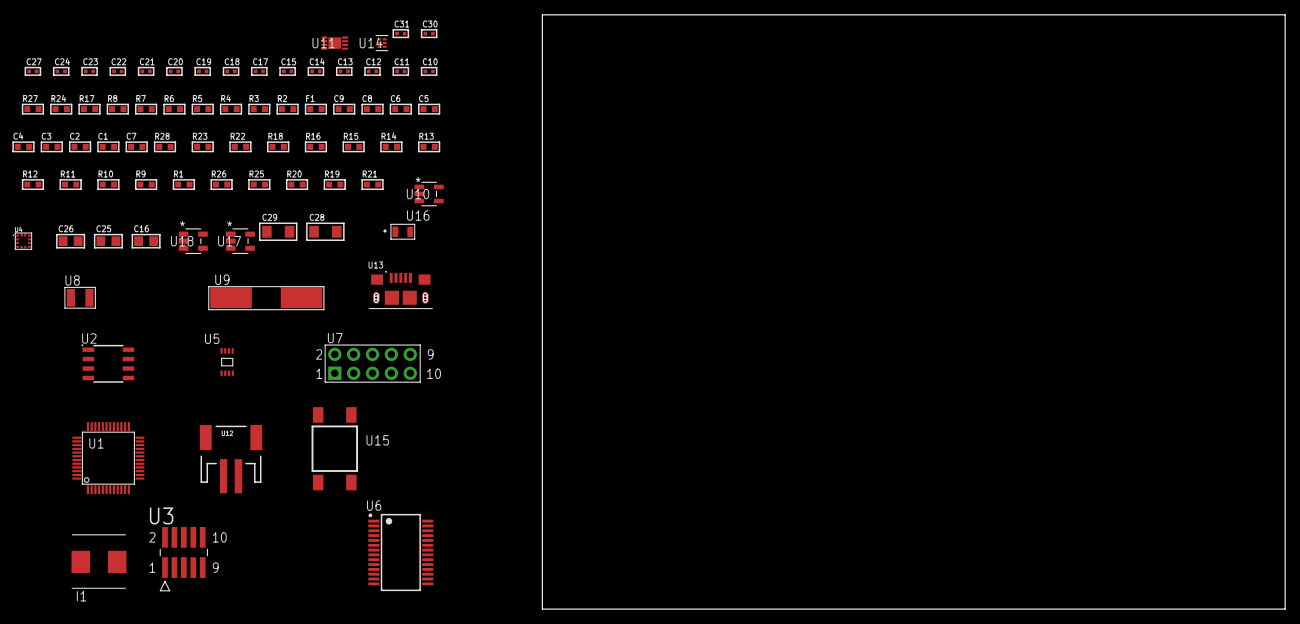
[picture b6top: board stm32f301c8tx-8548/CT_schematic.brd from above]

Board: 2 copper layers, 122.6 x 80.0 mm, 79 parts (0 on the bottom side), 54 nets, no tracks yet.

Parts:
C1, C9: 1e-06; C0603
C2, C3, C4, C5, C6: 1e-07; C0603
C7: 4.7e-06; C0603
C8: 1e-08; C0603
C10, C11, C12, C13: 1e-11; C0402
C14, C19, C30, C31: 1e-08; C0402
C15, C17, C18, C20, C21, C22, C23, C24, C27: 1e-07; C0402
C16, C25, C26: 1e-05; C0805
C28, C29: 1e-05; C1206
F1: 240.0; L0603
I1: 2e-06; WE-HCI_7030/7040/7050
R1, R9, R10, R11, R12, R13, R14, R15, R16, R18, R22, R23, R28: 10000.0; R0603
R2: 1000.0; R0603
R3: 1600.5; R0603
R4: 4700.0; R0603
R5, R6, R7, R8: 2200.0; R0603
R17: 5.0; R0603
R19: 100000.0; R0603
R20: 220000.0; R0603
R21: 1000000.0; R0603
R24: 9100.0; R0603
R25: 680000.0; R0603
R26: 120000.0; R0603
R27: 2000.0; R0603
U1: STM32F301C8T7; LQFP48
U2: AT25128B-SSHL-T; SOIC-8
U3: FTSH-105-01-L-DV-K; SAMTEC_FTSH-105-01-L-DV-K
U4: LIS2HH12TR; LGA-12
U5: 24AA02T-I/MNY; TDFN-8/6MM
U6: ST3241EBPR; SSOP-28
U7: HTSS-105-01-G-D
U8: ABS07-32.768KHZ-7-T
U9: ABLS-25.000MHZ-B2F-T
U10: ltc3406es5; TSOT-23-5
U11: MCP73831T-2ACI/MC; DFN8_2X3MC
U12: S2B-PH-SM4-TB(LF)(SN); JST-2-SMD
U13: 10118193-0001LF; FCI_10118193-0001LF
U14: TPS3895ADRYR; SON-6
U15: 4-1437565-2; SW_4-1437565-2
U16: Q65110A2395; LGM67K-G1J2-24-Z
U17, U18: nc7sz125m5x; NC7SZ125M5X

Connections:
CLK_CRYSTAL_U1_3: C10.1, U1.3, U8.1
CLK_CRYSTAL_U1_4: C11.1, U1.4, U8.2
CLK_CRYSTAL_U1_5: C12.1, U1.5, U9.1
CLK_CRYSTAL_U1_6: C13.1, U1.6, U9.2
GND: C1.2, C2.2, C3.2, C4.2, C5.2, C6.2, C7.2, C8.2, C9.2, C10.2, C11.2, C12.2, C13.2, C14.2, C15.2, C16.2, C17.2, C18.2, C19.2, C20.2, C23.2, C24.2, C25.2, C26.1, C26.2, C27.2, C28.2, C29.2, C30.2, C31.2, R2.2, R9.2, R16.2, R17.2, R20.2, R24.2, R26.2, R27.2, U1.8, U1.23, U1.35, U1.47, U2.4, U3.3, U3.5, U4.5, U4.6, U4.7, U4.8, U5.4, U6.23, U6.25, U7.9, U10.2, U11.6, U11.9, U12.2, U13.5, U13.6, U13.7, U13.8, U13.9, U14.2, U16.C, U17.2, U17.3, U18.1, U18.3
INPUT_USBPOWER_5V: C28.1, R28.2, U11.1, U11.2, U13.1
NET_U1_7: R4.1, U1.7, U18.4
NET_U1_9: C8.1, C9.1, F1.1, U1.9
NET_U1_30: R7.1, U1.30, U5.6
NET_U1_31: R8.1, U1.31, U5.5
NET_U1_40: R3.1, U1.40, U16.A
NET_U1_41: R1.1, U1.41, U15.3, U15.4
NET_U1_44: R9.1, U1.44
NET_U1_45: R5.1, U1.45, U4.1
NET_U1_46: R6.1, U1.46, U4.4
NET_U2_3: R10.1, U2.3
NET_U2_7: R12.1, U2.7
NET_U3_9: R17.1, U3.9
NET_U4_2: R18.1, U4.2
NET_U6_1: C22.1, U6.1
NET_U6_2: C22.2, U6.2
NET_U6_3: C24.1, U6.3
NET_U6_22: R19.1, U6.22
NET_U6_24: C21.2, U6.24
NET_U6_27: C23.1, U6.27
NET_U6_28: C21.1, U6.28
NET_U7_3: U6.4, U7.3
NET_U7_4: U6.5, U7.4
NET_U7_5: U6.9, U7.5
NET_U7_6: U6.10, U7.6
NET_U10_3: I1.1, U10.3
NET_U10_5: R20.1, R21.1, U10.5
NET_U10_ATNET_3: I1.2, R21.2
NET_U11_5: R28.1, U11.5
NET_U11_8: R27.1, U11.8
NET_U14_1: R23.1, R24.1, U14.1
NET_U14_3: R25.2, R26.1, U14.3
NET_U14_4: R22.1, U14.4, U17.4, U18.2
NET_U15_1: R2.1, U15.1, U15.2
PROC_SPI2_MISO: U1.27, U2.2
PROC_SPI2_MOSI: U1.28, U2.5
PROC_SPI2_NSS: R11.1, U1.25, U2.1
PROC_SPI2_SCK: U1.26, U2.6
PROC_SYS_JTCK_SWCLK: R16.1, U1.37, U3.4
PROC_SYS_JTDI: R14.1, U1.38, U3.8
PROC_SYS_JTDO_TRACESWO: U1.39, U3.6
PROC_SYS_JTMS_SWDIO: R15.1, U1.34, U3.2
PROC_USART1_CTS: U1.32, U6.13
PROC_USART1_RTS: U1.33, U6.18
PROC_USART1_RX: U1.43, U6.19
PROC_USART1_TX: U1.42, U6.14
RST_OUT_U3_JTAG_RST_B: R13.1, U3.10, U17.1
VCC_S1_3V7: C25.1, C29.1, U10.4, U11.3, U11.4, U12.1
VCC_TIER1_3V3: C1.1, C2.1, C3.1, C4.1, C5.1, C6.1, C7.1, C14.1, C15.1, C16.1, C17.1, C18.1, C19.1, C20.1, C26.2, C27.1, C30.1, C31.1, F1.2, I1.2, R1.2, R3.2, R4.2, R5.2, R6.2, R7.2, R8.2, R10.2, R11.2, R12.2, R13.2, R14.2, R15.2, R18.2, R19.2, R21.2, R22.2, R23.2, R25.1, U1.1, U1.24, U1.36, U1.48, U2.8, U3.1, U4.9, U4.10, U5.7, U5.8, U6.26, U14.6, U17.5, U18.5
